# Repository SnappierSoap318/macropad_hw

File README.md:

# macropad_hw
Hardware for macropad

# Bom
|#  |Reference                                                             |Qty|Value       |Footprint                                         |DNP|
|---|----------------------------------------------------------------------|---|------------|--------------------------------------------------|---|
|1  |BT1                                                                   |1  |Battery_Cell|Battery:BatteryHolder_MPD_BH-18650-PC2            |   |
|2  |C1                                                                    |1  |1uF         |Capacitor_THT:C_Disc_D4.3mm_W1.9mm_P5.00mm        |   |
|3  |C2                                                                    |1  |0.1uF       |Capacitor_THT:C_Disc_D4.3mm_W1.9mm_P5.00mm        |   |
|4  |D1, D2, D3, D4, D5, D6, D7, D8, D9, D10, D11, D12, D13, D14, D15, D16 |16 |LED         |Diode_SMD:D_1206_3216Metric                       |   |
|5  |H1, H2, H3, H4, H5, H6, H7, H8                                        |8  |MountingHole|MountingHole:MountingHole_2.5mm                   |   |
|6  |SW1                                                                   |1  |SW_SPST     |Button_Switch_THT:SW_CuK_JS202011CQN_DPDT_Straight|   |
|7  |U1                                                                    |1  |CD74HC4067M |Package_SO:SOIC-24W_7.5x15.4mm_P1.27mm            |   |
|8  |U2, U3, U4, U5, U6, U7, U8, U9, U10, U11, U12, U13, U14, U15, U16, U17|16 |~           |Gateron:Gatreon KS-20                             |   |
|9  |U18                                                                   |1  |~           |Nice!nano                                         |   |

this is aimed a wireless Analog macropad, any suggestions and changes are welcome.

PS, ik there isnt any holes to move the switches, have to add that in the next revision of the dxf files maybe.

PS:2, The code for running this is [here](https://github.com/SnappierSoap318/macropad)

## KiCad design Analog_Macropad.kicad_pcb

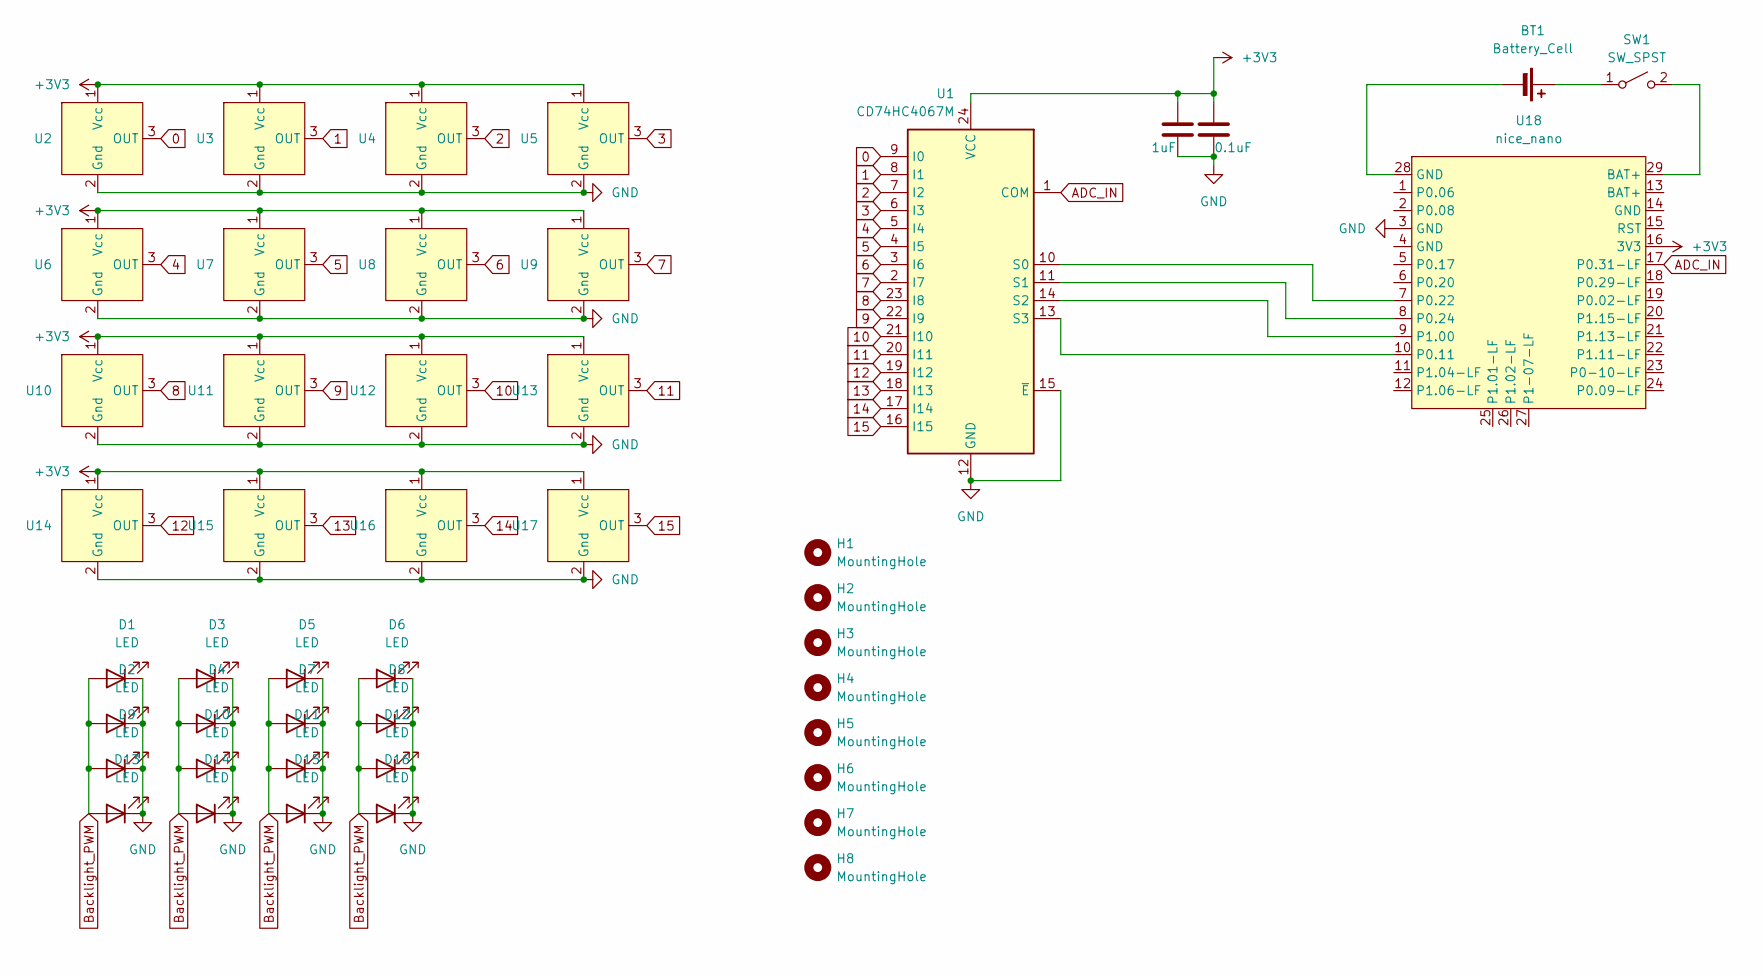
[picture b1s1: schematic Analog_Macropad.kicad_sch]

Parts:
BT1: Battery_Cell; BatteryHolder_MPD_BH-18650-PC2
C3: 1uF; C_Disc_D4.3mm_W1.9mm_P5.00mm
C4: 0.1uF; C_Disc_D4.3mm_W1.9mm_P5.00mm
D1, D2, D3, D4, D5, D6, D7, D8, D9, D10, D11, D12, D13, D14, D15, D16: LED; D_1206_3216Metric
H1, H2, H3, H4, H5, H6, H7, H8: MountingHole; MountingHole_2.5mm
SW1: SW_SPST; SW_CuK_JS202011CQN_DPDT_Straight
U1: CD74HC4067M; SOIC-24W_7.5x15.4mm_P1.27mm
U2, U3, U4, U5, U6, U7, U8, U9, U10, U11, U12, U13, U14, U15, U16, U17: Gatreon KS-20
U18: nice_nano; nice_nano_AH_USBup

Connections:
0: U1.9 (I0), U2.3 (OUT)
1: U1.8 (I1), U3.3 (OUT)
2: U1.7 (I2), U4.3 (OUT)
3: U1.6 (I3), U5.3 (OUT)
4: U1.5 (I4), U6.3 (OUT)
5: U1.4 (I5), U7.3 (OUT)
6: U1.3 (I6), U8.3 (OUT)
7: U1.2 (I7), U9.3 (OUT)
8: U1.23 (I8), U10.3 (OUT)
9: U1.22 (I9), U11.3 (OUT)
10: U1.21 (I10), U12.3 (OUT)
11: U1.20 (I11), U13.3 (OUT)
12: U1.19 (I12), U14.3 (OUT)
13: U1.18 (I13), U15.3 (OUT)
14: U1.17 (I14), U16.3 (OUT)
15: U1.16 (I15), U17.3 (OUT)
+3V3: U1.24 (VCC), U2.1 (Vcc), U3.1 (Vcc), U4.1 (Vcc), U5.1 (Vcc), U6.1 (Vcc), U7.1 (Vcc), U8.1 (Vcc), U9.1 (Vcc), U10.1 (Vcc), U11.1 (Vcc), U12.1 (Vcc), U13.1 (Vcc), U14.1 (Vcc), U15.1 (Vcc), U16.1 (Vcc), U17.1 (Vcc), U18.16 (3V3); also elsewhere on the board
ADC_IN: U1.1 (COM), U18.17 (P0.31-LF)
Backlight_PWM: D1.2 (A), D2.2 (A), D3.2 (A), D4.2 (A), D5.2 (A), D6.2 (A), D7.2 (A), D8.2 (A), D9.2 (A), D10.2 (A), D11.2 (A), D12.2 (A), D13.2 (A), D14.2 (A), D15.2 (A), D16.2 (A)
GND: D1.1 (K), D2.1 (K), D3.1 (K), D4.1 (K), D5.1 (K), D6.1 (K), D7.1 (K), D8.1 (K), D9.1 (K), D10.1 (K), D11.1 (K), D12.1 (K), D13.1 (K), D14.1 (K), D15.1 (K), D16.1 (K), U1.12 (GND), U1.15 (~E), U2.2 (Gnd), U3.2 (Gnd), U4.2 (Gnd), U5.2 (Gnd), U6.2 (Gnd), U7.2 (Gnd), U8.2 (Gnd), U9.2 (Gnd), U10.2 (Gnd), U11.2 (Gnd), U12.2 (Gnd), U13.2 (Gnd), U14.2 (Gnd), U15.2 (Gnd), U16.2 (Gnd), U17.2 (Gnd), U18.3 (GND); also elsewhere on the board
unnamed: BT1.1 (+), SW1.1 (A)
unnamed: BT1.2 (-), U18.28 (GND)
unnamed: SW1.2 (B), U18.29 (BAT+)
unnamed: U1.10 (S0), U18.7 (P0.22)
unnamed: U1.11 (S1), U18.8 (P0.24)
unnamed: U1.14 (S2), U18.9 (P1.00)
unnamed: U1.13 (S3), U18.10 (P0.11)

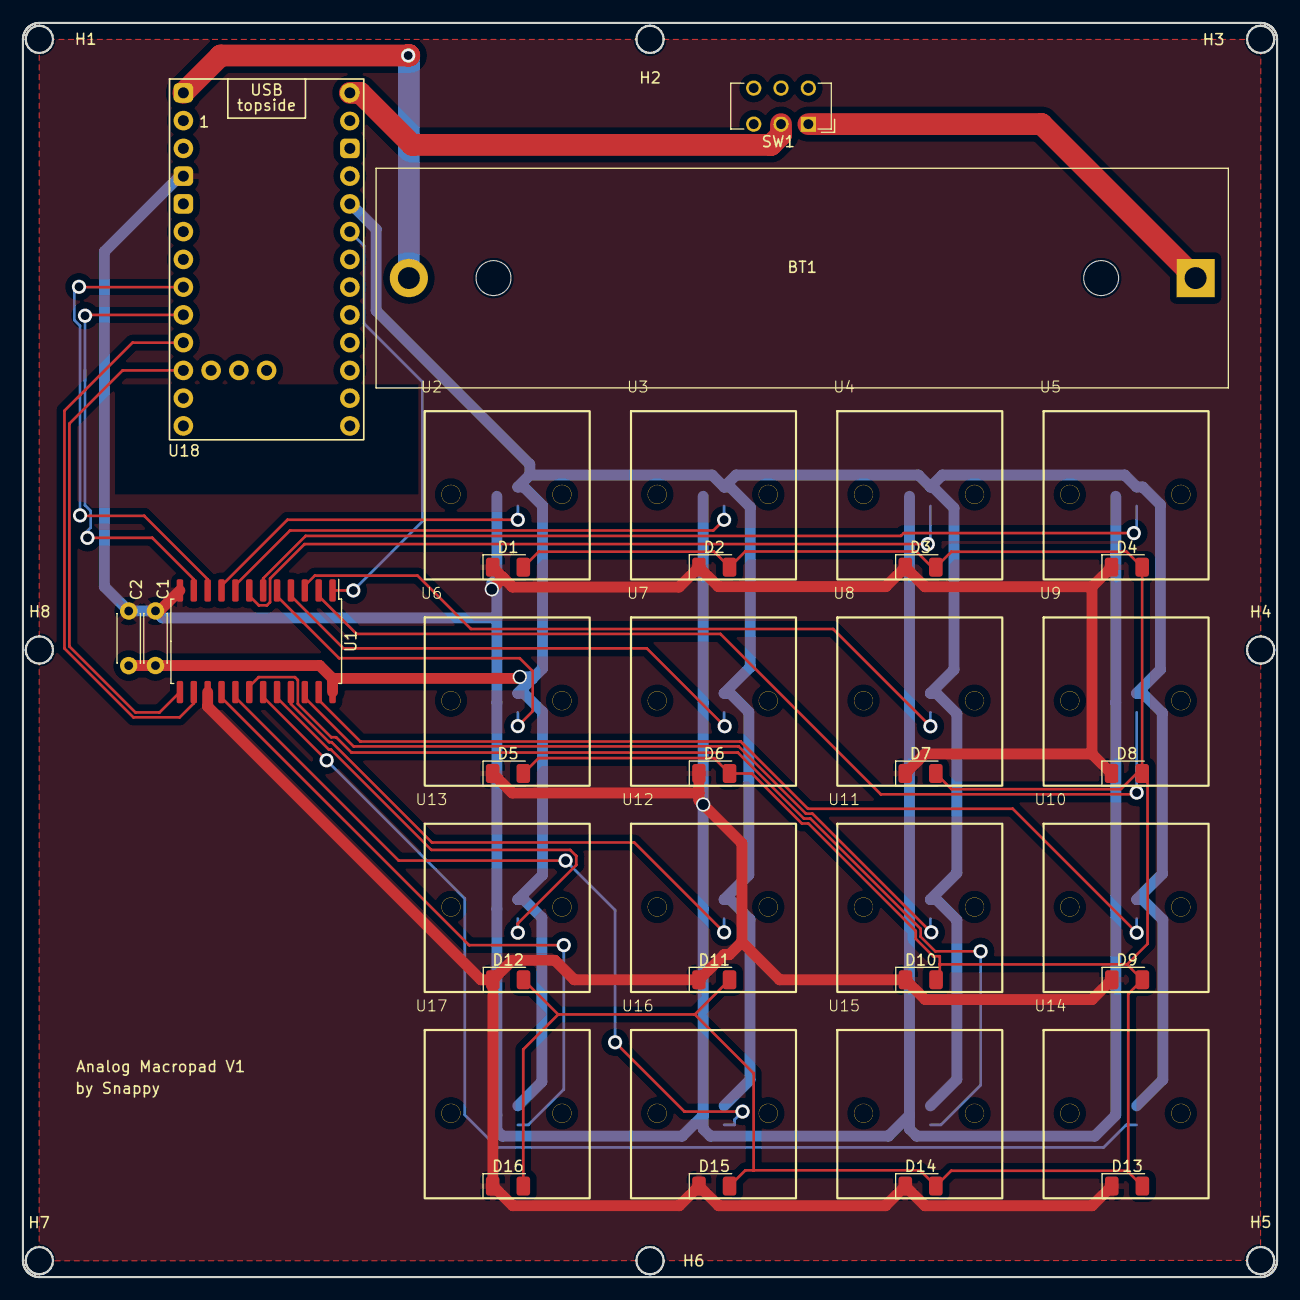
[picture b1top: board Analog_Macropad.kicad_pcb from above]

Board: 2 copper layers, 114.8 x 114.8 mm, 46 parts (0 on the bottom side), 27 nets.

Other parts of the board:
C1: 1uF; C_Disc_D4.3mm_W1.9mm_P5.00mm
C2: 0.1uF; C_Disc_D4.3mm_W1.9mm_P5.00mm

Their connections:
+3V3: C1.2, C2.1; also elsewhere on the board
GND: C1.1, C2.2; also elsewhere on the board

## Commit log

2024-05-21 Add Laser cut files
2024-05-21 Added Schematic, PCB layout and custom footprint
2024-05-21 Added Gerber files
2024-05-21 add 3d files
2024-05-23 update laser cut files to fix dimensions
